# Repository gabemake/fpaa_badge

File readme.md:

# FPAA Add-on for SuperCon 2023 badge

## SuperCon Badge info
Main article: https://hackaday.com/2023/10/18/2023-hackaday-supercon-badge-welcome-to-the-vectorscope/

Key points:
- RP2040 with DAC/ADC connected to PIOs
- Round display also on PIOs
- Micropython based SW

## FPAA Addon concept

What is an FPAA?
- Field-Programmable Analog Array
- Configurable array of analog components
  - Gain
  - Filter
  - Mix
  - more...
- 4 differential I and O ports
- 3 bidirectional differential ports
- SPI-ish configuration interface
- a.k.a. dpASP
- Datasheet: https://www.anadigm.com/_doc/DS231000-U001.pdf

Other things on the board:
- Connectors and single-to-differential conversion matching to badge IO
- ESP32-S3 to program FPAA (via web or otherwise)
- RBGLEDs all the way around
- a button
- BNC connectors + 3.5mm jack for external inputs or output
- SD Card reader

What to do with the addon?
- Figure out how to program and use a FPAA
- Maybe do a cool windows media player -like visualizer for music
- Get lots of practice soldering 0603 resistors

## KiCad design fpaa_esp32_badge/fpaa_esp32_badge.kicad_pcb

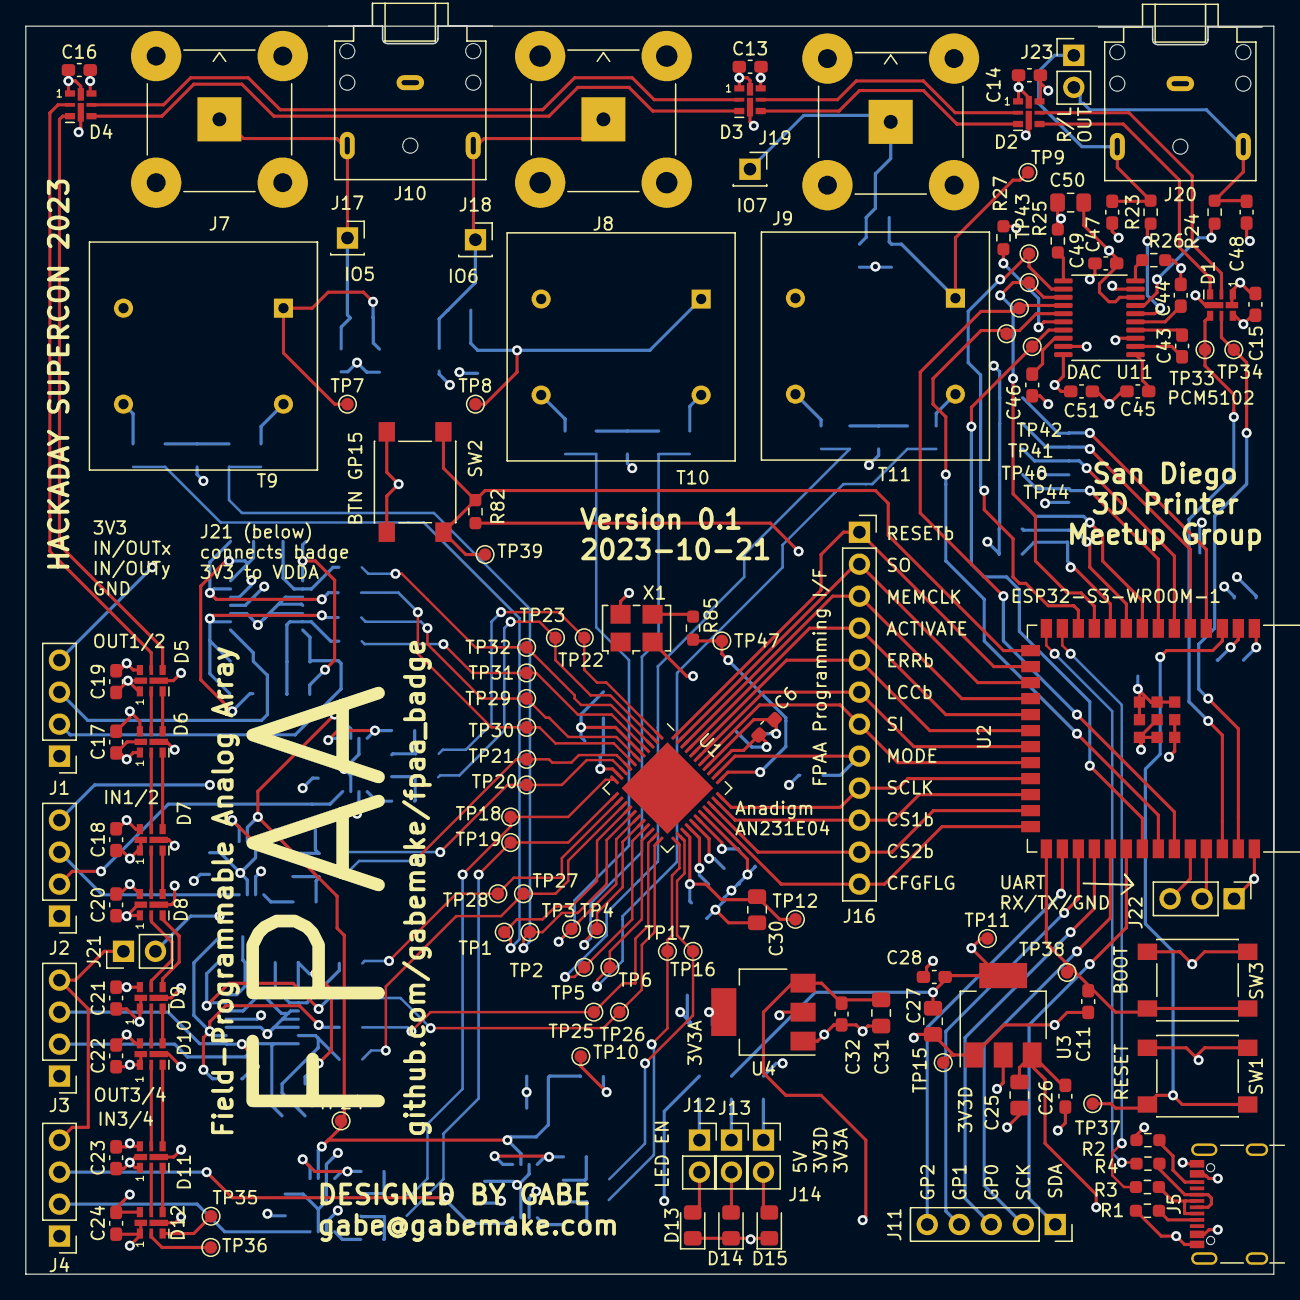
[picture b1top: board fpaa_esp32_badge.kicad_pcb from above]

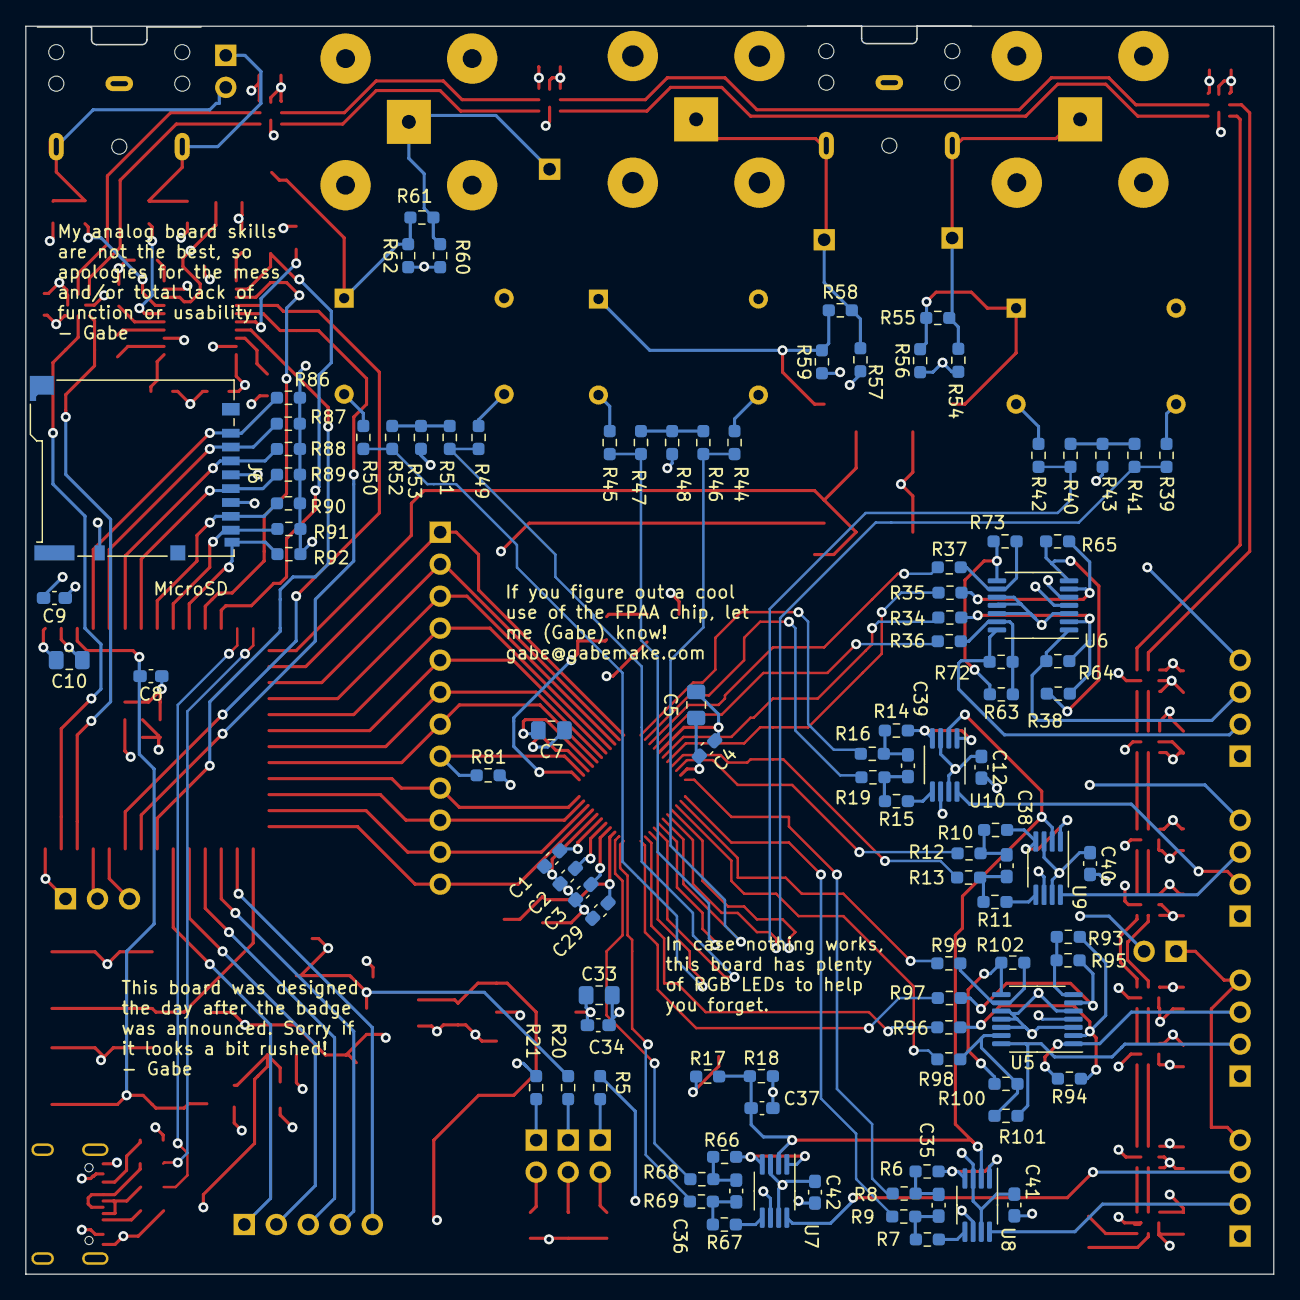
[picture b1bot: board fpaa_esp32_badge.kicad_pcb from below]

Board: 4 copper layers, 99.1 x 99.1 mm, 233 parts (101 on the bottom side), 168 nets.

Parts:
C1, C2, C3, C4, C6, C8, C9, C11, C12, C13, C14, C15, C16, C17, C18, C19, C20, C21, C22, C23, C24, C26, C28, C29, C32, C34, C37, C40, C41, C42, C49, C51: 100nF; C_0603_1608Metric_Pad1.08x0.95mm_HandSolder
C5, C7, C10, C25, C27, C30, C31, C33, C50: 10uF; C_0805_2012Metric_Pad1.18x1.45mm_HandSolder
C35, C36, C38, C39, C47, C48: 2.2nF; C_0603_1608Metric_Pad1.08x0.95mm_HandSolder
C43, C44, C45, C46: 2.2uF; C_0603_1608Metric_Pad1.08x0.95mm_HandSolder
D1, D2, D3, D4, D5, D6, D7, D8, D9, D10, D11, D12: APA102-2020; LED-APA102-2020
D13, D14, D15: LED; LED_0805_2012Metric_Pad1.15x1.40mm_HandSolder
J1, J2, J3, J4: Conn_01x04; PinHeader_1x04_P2.54mm_Vertical
J5: USB_C_Receptacle_USB2.0; USB_C_Receptacle_GCT_USB4105-xx-A_16P_TopMnt_Horizontal
J6: Micro_SD_Card_Det1; microSD_HC_Hirose_DM3BT-DSF-PEJS
J7, J9: Conn_Coaxial; BNC_TEConnectivity_1478035_Horizontal
J8: Conn_Coaxial; BNC_Molex_SD-73131-024_Horizontal
J10, J20: AudioPlug3; Jack_3.5mm_CUI_SJ1-3523N_Horizontal
J11: Conn_01x05; PinSocket_1x05_P2.54mm_Vertical
J12, J13, J14: Conn_01x02; PinSocket_1x02_P2.54mm_Vertical
J16: Conn_01x12; PinSocket_1x12_P2.54mm_Vertical
J17, J18, J19: Conn_01x01; PinSocket_1x01_P2.54mm_Vertical
J21, J23: Conn_01x02; PinHeader_1x02_P2.54mm_Vertical
J22: Conn_01x03; PinHeader_1x03_P2.54mm_Vertical
R1, R2: 5.1K; R_0603_1608Metric_Pad0.98x0.95mm_HandSolder
R3, R4: 22; R_0603_1608Metric_Pad0.98x0.95mm_HandSolder
R5: 180; R_0603_1608Metric_Pad0.98x0.95mm_HandSolder
R6, R7, R10, R11, R14, R15, R66, R67: 250; R_0603_1608Metric_Pad0.98x0.95mm_HandSolder
R8, R9, R12, R13, R16, R19, R25, R26, R27, R39, R40, R42, R44, R45, R47, R49, R50, R52, R55, R58, R61, R68, R69: 0; R_0603_1608Metric_Pad0.98x0.95mm_HandSolder
R17, R18, R34, R35, R36, R37, R38, R63, R65, R73, R82, R85, R93, R95, R96, R97, R98, R99, R100, R102: 1K; R_0603_1608Metric_Pad0.98x0.95mm_HandSolder
R20, R21: 82; R_0603_1608Metric_Pad0.98x0.95mm_HandSolder
R23, R24: 470; R_0603_1608Metric_Pad0.98x0.95mm_HandSolder
R41, R43, R46, R48, R51, R53, R54, R56, R57, R59, R60, R62: DNP; R_0603_1608Metric_Pad0.98x0.95mm_HandSolder
R64, R72, R94, R101: RF; R_0603_1608Metric_Pad0.98x0.95mm_HandSolder
R81: 50; R_0603_1608Metric_Pad0.98x0.95mm_HandSolder
R86, R87, R88, R89, R90, R91, R92: 10K; R_0603_1608Metric_Pad0.98x0.95mm_HandSolder
SW1, SW2, SW3: SW_Push; SW_SPST_PTS645
T9, T10, T11: Transformer_1P_1S; Transformer_NF_ETAL_1-1_P1200
TP1, TP2, TP3, TP4, TP5, TP6, TP7, TP8, TP9, TP10, TP11, TP12, TP15, TP16, TP17, TP18, TP19, TP20, TP21, TP22, TP23, TP24, TP25, TP26, TP27, TP28, TP29, TP30, TP31, TP32, TP33, TP34, TP35, TP36, TP37, TP38, TP39, TP40, TP41, TP42, TP43, TP44, TP47: TestPoint; TestPoint_Pad_D1.0mm
U1: QFN-44-1EP_7x7mm_P0.5mm_EP5.15x5.15mm
U2: ESP32-S3-WROOM-1
U3: AMS1117-3.3; SOT-223-3_TabPin2
U4: AZ1117-3.3; SOT-223-3_TabPin2
U5, U6: LM324; TSSOP-14_4.4x5mm_P0.65mm
U7, U8, U9, U10: LT6350IMS8_PBF; MSOP-8_3x3mm_P0.65mm
U11: PCM5102; TSSOP-20_4.4x6.5mm_P0.65mm
X1: SG-5032CAN; Oscillator_SMD_SeikoEpson_SG8002LB-4Pin_5.0x3.2mm

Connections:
+3.3V: C6.1, C7.1, C9.1, C10.1, C27.1, C28.1, C51.1, J6.4 (VDD), R20.1, R82.1, R86.2, R87.2, R88.2, R89.2, R90.2, R91.2, R92.2, TP11.1, U1.36 (DVDD), U2.2 (3V3), U3.2 (VO), U11.20 (DVDD)
+5V: C13.1, C14.1, C15.1, C16.1, C17.1, C18.1, C19.1, C20.1, C21.1, C22.1, C23.1, C24.1, C25.1, C26.1, C31.1, C32.1, D1.1 (VDD), D2.1 (VDD), D3.1 (VDD), D4.1 (VDD), D5.1 (VDD), D6.1 (VDD), D7.1 (VDD), D8.1 (VDD), D9.1 (VDD), D10.1 (VDD), D11.1 (VDD), D12.1 (VDD), J5.A4 (VBUS), J5.A9 (VBUS), J5.B4 (VBUS), J5.B9 (VBUS), R5.1, U3.3 (VI), U4.3 (VI)
/Baluns/I1N: R19.2, TP23.1, U1.2 (I1N)
/Baluns/I1P: R16.2, TP22.1, U1.1 (I1P)
/Baluns/I1U: J2.2, U10.8 (+IN1)
/Baluns/I2N: R13.2, TP21.1, U1.8 (I2N)
/Baluns/I2P: R12.2, TP20.1, U1.9 (I2P)
/Baluns/I2U: J2.3, U9.8 (+IN1)
/Baluns/I3N: R9.2, TP19.1, U1.12 (I3N)
/Baluns/I3P: R8.2, TP18.1, U1.11 (I3P)
/Baluns/I3U: J4.2, U8.8 (+IN1)
/Baluns/I4N: R69.2, TP17.1, U1.23 (I4N)
/Baluns/I4P: R68.2, TP16.1, U1.24 (I4P)
/Baluns/I4U: J4.3, U7.8 (+IN1)
/Baluns/O1N: R37.1, TP32.1, U1.3 (O1N)
/Baluns/O1P: R36.1, TP31.1, U1.4 (O1P)
/Baluns/O1U: J1.2, R72.2, U6.14
/Baluns/O2N: R35.1, TP30.1, U1.7 (O2N)
/Baluns/O2P: R34.1, TP29.1, U1.6 (O2P)
/Baluns/O2U: J1.3, R64.2, U6.1
/Baluns/O3N: R99.1, TP28.1, U1.13 (O3N)
/Baluns/O3P: R98.1, TP27.1, U1.14 (O3P)
/Baluns/O3U: J3.2, R101.2, U5.14
/Baluns/O4N: R97.1, TP26.1, U1.22 (O4N)
/Baluns/O4P: R96.1, TP25.1, U1.21 (O4P)
/Baluns/O4U: J3.3, R94.2, U5.1
/DAC/I2S_BCK: TP42.1, U2.11 (GPIO18/U1RXD/ADC2_CH7/CLK_OUT3), U11.13 (BCK)
/DAC/I2S_DAT: TP41.1, U2.35 (MTMS/GPIO42), U11.14 (DIN)
/DAC/I2S_DEMP: R26.1, U11.10 (DEMP)
/DAC/I2S_FLT: R25.1, U11.11 (FLT)
/DAC/I2S_FMT: R27.1, U11.16 (FMT)
/DAC/I2S_LRCK: TP40.1, U2.34 (MTDI/GPIO41/CLK_OUT1), U11.15 (LRCK)
/DAC/I2S_SCK: TP43.1, U2.12 (GPIO8/TOUCH8/ADC1_CH7/SUBSPICS1), U11.12 (SCK)
/DAC/I2S_XSMT: TP44.1, U2.33 (MTDO/GPIO40/CLK_OUT2), U11.17 (XSMT)
/Jacks/IO5N: R40.2, R42.1, TP2.1, U1.16 (IO5N)
/Jacks/IO5P: R39.2, R41.1, TP1.1, U1.15 (IO5P)
/Jacks/IO6N: R45.2, R47.1, TP4.1, U1.18 (IO6N)
/Jacks/IO6P: R44.2, R46.1, TP3.1, U1.17 (IO6P)
/Jacks/IO7N: R50.2, R52.1, TP6.1, U1.20 (IO7N)
/Jacks/IO7P: R49.2, R51.1, TP5.1, U1.19 (IO7P)
/LEDs/RGB_CLK: D1.5 (CKI), TP34.1, U2.39 (GPIO1/TOUCH1/ADC1_CH0)
/LEDs/RGB_DAT: D1.4 (SDI), TP33.1, U2.38 (GPIO2/TOUCH2/ADC1_CH1)
/esp32/BOOT: C11.2, SW3.1, TP38.1, U2.27 (GPIO0/BOOT)
/esp32/BUTTON: R82.2, SW2.1, TP39.1, U2.15 (GPIO3/TOUCH3/ADC1_CH2)
/esp32/FPAA_ACTIVATE: J16.4, U1.41 (ACTIVATE), U2.19 (GPIO11/TOUCH11/ADC2_CH0/FSPID/FSPIIO5/S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)
/esp32/FPAA_CFGFLG: J16.12, U1.30 (CFGFLG), U2.26 (GPIO45)
/esp32/FPAA_CS1b: J16.10, U1.32 (CS1b), U2.24 (GPIO47/SPICLK_P/SUBSPICLK_P_DIFF)
/esp32/FPAA_CS2b: J16.11, U1.31 (CS2b), U2.25 (GPIO48/SPICLK_N/SUBSPICLK_N_DIFF)
/esp32/FPAA_ERRb: J16.5, U1.40 (ERRb), U2.20 (GPIO12/TOUCH12/ADC2_CH1/FSPICLK/FSPIIO6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)
/esp32/FPAA_LCCb: J16.6, U1.39 (LCCb/DOUT1), U2.21 (GPIO13/TOUCH13/ADC2_CH2/FSPIQ/FSPIIO7/S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)
/esp32/FPAA_MEMCLK: J16.3, U1.42 (MEMCLK/DOUT2), U2.18 (GPIO10/TOUCH10/ADC1_CH9/FSPICS0/FSPIIO4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)
/esp32/FPAA_RESETb: J16.1, U1.44 (RESETb), U2.16 (GPIO46)
/esp32/FPAA_SCLK: J16.9, U1.33 (SCLK), U2.23 (GPIO21)
/esp32/FPAA_SI: J16.7, U1.38 (SI), U2.22 (GPIO14/TOUCH14/ADC2_CH3/FSPIWP/FSPIDQS/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)
/esp32/FPAA_SO: J16.2, U1.43 (SO), U2.17 (GPIO9/TOUCH9/ADC1_CH8/FSPIHD/SUBSPIHD)
/esp32/RESET_N: C8.2, SW1.1, TP37.1, U2.3 (EN)
/esp32/SAO_GP0: J11.3, U2.30 (SPIDQS/GPIO37/FSPIQ/SUBSPIQ)
/esp32/SAO_GP1: J11.4, U2.29 (SPIIO7/GPIO36/FSPICLK/SUBSPICLK)
/esp32/SAO_GP2: J11.5, U2.28 (SPIIO6/GPIO35/FSPID/SUBSPID)
/esp32/SAO_SCK: J11.2, U2.31 (GPIO38/FSPIWP/SUBSPIWP)
/esp32/SAO_SDA: J11.1, U2.32 (MTCK/GPIO39/CLK_OUT3/SUBSPICS1)
/esp32/SD_CLK: J6.5 (CLK), R89.1, U2.7 (GPIO7/TOUCH7/ADC1_CH6)
/esp32/SD_CMD: J6.3 (CMD), R88.1, U2.6 (GPIO6/TOUCH6/ADC1_CH5)
/esp32/SD_DAT0: J6.7 (DAT0), R90.1, U2.8 (GPIO15/U0RTS/ADC2_CH4/XTAL_32K_P)
/esp32/SD_DAT1: J6.8 (DAT1), R91.1, U2.9 (GPIO16/U0CTS/ADC2_CH5/XTAL_32K_N)
/esp32/SD_DAT2: J6.1 (DAT2), R86.1, U2.4 (GPIO4/TOUCH4/ADC1_CH3)
/esp32/SD_DAT3: J6.2 (DAT3/CD), R87.1, U2.5 (GPIO5/TOUCH5/ADC1_CH4)
/esp32/SD_DET: J6.9 (DET), R92.1, U2.10 (GPIO17/U1TXD/ADC2_CH6)
/esp32/UART_RX: J22.3, U2.36 (U0RXD/GPIO44/CLK_OUT2)
/esp32/UART_TX: J22.2, U2.37 (U0TXD/GPIO43/CLK_OUT1)
/esp32/USB_N: R3.1, U2.13 (GPIO19/U1RTS/ADC2_CH8/CLK_OUT2/USB_D-)
/esp32/USB_P: R4.1, U2.14 (GPIO20/U1CTS/ADC2_CH9/CLK_OUT1/USB_D+)
GND: C1.2, C2.1, C3.2, C4.2, C5.2, C6.2, C7.2, C8.1, C9.2, C10.2, C11.1, C12.2, C13.2, C14.2, C15.2, C16.2, C17.2, C18.2, C19.2, C20.2, C21.2, C22.2, C23.2, C24.2, C25.2, C26.2, C27.2, C28.2, C29.2, C30.2, C31.2, C32.2, C33.2, C34.2, C37.2, C40.2, C41.2, C42.2, C44.2, C45.2, C46.2, C47.2, C48.2, C49.2, C50.2, C51.2, D1.6 (GND), D2.6 (GND), D3.6 (GND), D4.6 (GND), D5.6 (GND), D6.6 (GND), D7.6 (GND), D8.6 (GND), D9.6 (GND), D10.6 (GND), D11.6 (GND), D12.6 (GND), D13.1 (K), D14.1 (K), D15.1 (K), J1.1, J2.1, J3.1, J4.1, J5.A1 (GND), J5.A12 (GND), J5.B1 (GND), J5.B12 (GND), J5.S1 (SHIELD), J6.6 (VSS), J6.10 (SHIELD), J7.2 (Ext), J8.2 (Ext), J9.2 (Ext), J10.S, J20.S, J22.1, R1.1, R2.1, R18.2, R25.2, R26.2, R27.2, R43.2, R48.2, R53.2, R54.1, R56.1, R57.1, R59.1, R60.1, R62.1, R81.2, SW1.2, SW2.2, SW3.2, TP15.1, U1.5 (AVSS), U1.29 (BVSS), U1.37 (DVSS), U2.1 (GND), U2.40 (GND), U2.41 (GND), U3.1 (GND), U4.1 (GND), U5.3 (+), U5.5 (+), U5.10 (+), U5.11 (V-), U5.12 (+), U6.3 (+), U6.5 (+), U6.10 (+), U6.11 (V-), U6.12 (+), U7.6 (V-), U8.6 (V-), U9.6 (V-), U10.6 (V-), U11.3 (CPGND), U11.9 (AGND), U11.19 (DGND), X1.2 (GND)
unnamed: C35.1, R6.2, R8.1
unnamed: C35.2, R7.2, R9.1
unnamed: C36.1, R66.2, R68.1
unnamed: C36.2, R67.2, R69.1
unnamed: C38.1, R10.2, R12.1
unnamed: C38.2, R11.2, R13.1
unnamed: C39.1, R14.2, R16.1
unnamed: C39.2, R15.2, R19.1
unnamed: D1.2 (CKO), D2.5 (CKI)
unnamed: D1.3 (SDO), D2.4 (SDI)
unnamed: D2.2 (CKO), D3.5 (CKI)
unnamed: D2.3 (SDO), D3.4 (SDI)
unnamed: D3.2 (CKO), D4.5 (CKI)
unnamed: D3.3 (SDO), D4.4 (SDI)
unnamed: D4.2 (CKO), D5.5 (CKI)
unnamed: D4.3 (SDO), D5.4 (SDI)
unnamed: D5.2 (CKO), D6.5 (CKI)
unnamed: D5.3 (SDO), D6.4 (SDI)
unnamed: D6.2 (CKO), D7.5 (CKI)
unnamed: D6.3 (SDO), D7.4 (SDI)
unnamed: D7.2 (CKO), D8.5 (CKI)
unnamed: D7.3 (SDO), D8.4 (SDI)
unnamed: D8.2 (CKO), D9.5 (CKI)
unnamed: D8.3 (SDO), D9.4 (SDI)
unnamed: D9.2 (CKO), D10.5 (CKI)
unnamed: D10.2 (CKO), D11.5 (CKI)
unnamed: D9.3 (SDO), D10.4 (SDI)
unnamed: D10.3 (SDO), D11.4 (SDI)
unnamed: D11.2 (CKO), D12.5 (CKI)
unnamed: D11.3 (SDO), D12.4 (SDI)
unnamed: D12.2 (CKO), TP36.1
unnamed: D12.3 (SDO), TP35.1
unnamed: D13.2 (A), J12.2
unnamed: D14.2 (A), J13.2
unnamed: D15.2 (A), J14.2
unnamed: J5.A5 (CC1), R1.2
unnamed: J5.B5 (CC2), R2.2
unnamed: J5.A6 (D+), J5.B6 (D+), R4.2
unnamed: J5.A7 (D-), J5.B7 (D-), R3.2
unnamed: J12.1, R5.2
unnamed: J13.1, R20.2
unnamed: J14.1, R21.2
unnamed: J16.8, R81.1, U1.35 (MODE)
unnamed: J7.1 (In), J10.T, J17.1, R54.2, R55.1
unnamed: J8.1 (In), J10.R, J18.1, R57.2, R58.1
unnamed: J9.1 (In), J19.1, R60.2, R61.1
unnamed: J3.4, J4.4, J21.1
unnamed: C47.1, J20.T, J23.1, R23.2
unnamed: C48.1, J20.R, J23.2, R24.2
unnamed: R38.2, R65.2, U6.7
unnamed: R41.2, R42.2, R43.1
unnamed: R46.2, R47.2, R48.1
unnamed: R51.2, R52.2, R53.1
unnamed: R63.2, R73.2, U6.8
unnamed: R93.2, R95.2, U5.7
unnamed: R100.2, R102.2, U5.8
unnamed: R55.2, R56.2, T9.1 (AA), TP7.1
unnamed: R40.1, T9.3 (SA)
unnamed: R39.1, T9.4 (SB)
unnamed: R58.2, R59.2, T10.1 (AA), TP8.1
unnamed: R45.1, T10.3 (SA)
unnamed: R44.1, T10.4 (SB)
unnamed: R61.2, R62.2, T11.1 (AA), TP9.1
unnamed: R50.1, T11.3 (SA)
unnamed: R49.1, T11.4 (SB)
unnamed: R85.2, TP47.1, U1.34 (ACLK)
unnamed: C2.2, U1.27 (VMR)
unnamed: C1.1, U1.28 (VREFN)
unnamed: C3.1, U1.26 (VREFP)
unnamed: R93.1, R94.1, R96.2, U5.2 (-)
unnamed: R95.1, R97.2, U5.6 (-)
unnamed: R99.2, R102.1, U5.9 (-)
unnamed: R98.2, R100.1, R101.1, U5.13 (-)
unnamed: R34.2, R38.1, R64.1, U6.2 (-)
unnamed: R35.2, R65.1, U6.6 (-)
unnamed: R37.2, R73.1, U6.9 (-)
unnamed: R36.2, R63.1, R72.1, U6.13 (-)
unnamed: R66.1, U7.1 (-IN1), U7.4 (OUT1)
unnamed: R67.1, U7.5 (OUT2)
unnamed: R6.1, U8.1 (-IN1), U8.4 (OUT1)
unnamed: R7.1, U8.5 (OUT2)
unnamed: R10.1, U9.1 (-IN1), U9.4 (OUT1)
unnamed: R11.1, U9.5 (OUT2)
unnamed: C37.1, R17.2, R18.1, TP24.1, U7.2 (+IN2), U8.2 (+IN2), U9.2 (+IN2), U10.2 (+IN2)
unnamed: R14.1, U10.1 (-IN1), U10.4 (OUT1)
unnamed: R15.1, U10.5 (OUT2)
unnamed: C43.2, U11.4 (CAPM)
unnamed: C43.1, U11.2 (CAPP)
unnamed: C45.1, U11.1 (CPVDD)
unnamed: C46.1, U11.18 (LDOO)
unnamed: R23.1, U11.6 (OUTL)
unnamed: R24.1, U11.7 (OUTR)
unnamed: C44.1, U11.5 (VNEG)
unnamed: R85.1, X1.3 (OUT)
VDDA: C4.1, C5.1, C12.1, C29.1, C30.1, C33.1, C34.1, C40.1, C41.1, C42.1, C49.1, C50.1, J1.4, J2.4, J21.2, R17.1, R21.1, TP10.1, TP12.1, U1.10 (AVDD), U1.25 (BVDD), U4.2 (VO), U5.4 (V+), U6.4 (V+), U7.3 (V+), U7.7 (~SHDN), U8.3 (V+), U8.7 (~SHDN), U9.3 (V+), U9.7 (~SHDN), U10.3 (V+), U10.7 (~SHDN), U11.8 (AVDD), X1.4 (VCC)

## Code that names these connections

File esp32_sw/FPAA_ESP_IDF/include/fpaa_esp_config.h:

#define BADGE_ESP_WIFI_SSID      "FPAA Badge"
#define BADGE_ESP_WIFI_PASS      "security through obscurity"
#define BADGE_ESP_WIFI_CHANNEL   11
#define BADGE_MAX_STA_CONN       10

#define FPAA_HOST    SPI2_HOST

#define FPAA_SO_PIN 9
#define FPAA_SI_PIN 14
#define FPAA_SCLK_PIN 21
#define FPAA_CS1B_PIN 47

#define FPAA_RESETB_PIN 46
#define FPAA_MEMCLK_PIN 10
#define FPAA_ACTIVATE_PIN 11
#define FPAA_ERRB_PIN 12
#define FPAA_LCCB_PIN 13
#define FPAA_CS2B_PIN 48
#define FPAA_CFGFLG_PIN 45
#define FPAA_OUTPUT_PINS  ((1ULL<<FPAA_RESETB_PIN) | (1ULL<<FPAA_CS2B_PIN))
#define FPAA_HOLD_PINS  (1ULL<<FPAA_ERRB_PIN)

#define FPAA_PROG_MAX_BYTES 3204 // based on the only file I have
#define FPAA_PROG_SCK_HZ 10000000 // 10 MHz for now

// I2S Configuration
#define I2S_BLK_PIN 18
#define I2S_WS_PIN 41
#define I2S_DATA_OUT_PIN 40
#define I2S_DATA_IN_PIN I2S_GPIO_UNUSED
#define I2S_SCLK_PIN 8

//Storage config (comment for internal flash)
//#define USE_SD_CARD
#define USE_SDMMC_MODE

// SDMMC Configuration (default for ESP32-WROVER-E)
#define SDMMC_CMD_PIN 6
#define SDMMC_CLK_PIN 7
#define SDMMC_D0_PIN 15
#define SDMMC_D1_PIN 16
#define SDMMC_D2_PIN 4
#define SDMMC_D3_PIN 5

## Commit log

2023-10-22 Initial commit: schematics for v0.1 as ordered
2023-10-24 added pdf and corrected some part values
2023-11-01 started software... more to go.
2023-11-01 got web file management working with internal flash and FPAA program
2023-11-01 added resources and updated readme
2023-11-02 added interactive html bom
2023-11-02 Updated html bom with all values
2023-11-04 add a data directory with test file
2023-11-04 Support upload from data folder to SPIFFS
2023-11-05 Integrate web socket service into http server
2023-11-06 FPAA programming works, added script to convert .ahf to binary
